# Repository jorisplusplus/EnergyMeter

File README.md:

PCB and esphome configuration for reading P1 smart meter and RS485 Modbus devices (pv systems)

## Hardware ##
Hardware production files are found in the production folder. These files can be generated with the generate.sh command (requires kikit to be installed).

## ESPHOME ##
In the esphome folder there are 2 configuration files for P1 Meter and Goodwe xs inverter. Note both configurations use the ethernet port

## Housing ##
In the Housing folder the openscad and stl files are present. The pcb should fit pressfit in the housing.

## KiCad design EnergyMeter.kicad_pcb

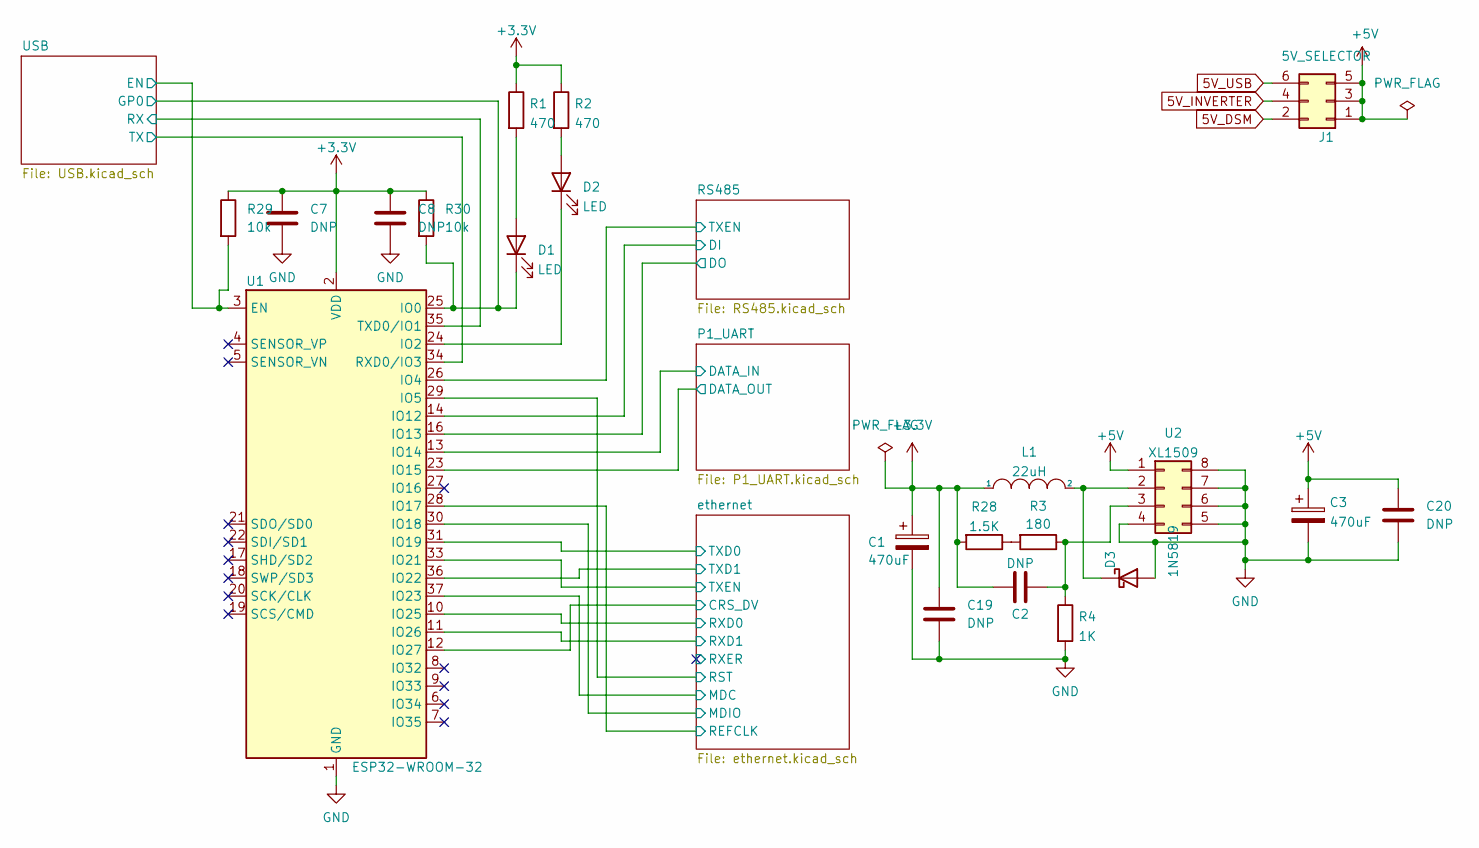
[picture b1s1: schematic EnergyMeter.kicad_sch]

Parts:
C1, C3: 470uF; CP_Radial_D8.0mm_P3.50mm; LCSC C1590895
C2, C7, C8, C19, C20: DNP; C_0603_1608Metric
D1, D2: LED; LED_0805_2012Metric; LCSC C84256
D3: 1N5819; D_SOD-323; LCSC C191023
J1: 5V_SELECTOR; PinHeader_2x03_P2.54mm_Horizontal
L1: 22uH; L_Taiyo-Yuden_NR-40xx; LCSC C83472
R1, R2: 470; R_0603_1608Metric; LCSC C23179
R3: 180; R_0603_1608Metric; LCSC C22828
R4: 1K; R_0603_1608Metric; LCSC C21190
R28: 1.5K; R_0603_1608Metric; LCSC C22843
R29, R30: 10k; R_0603_1608Metric
U1: ESP32-WROOM-32; LCSC C82899
U2: XL1509; SOP-8_3.9x4.9mm_P1.27mm; LCSC C74192

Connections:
5V_DSM: J1.2; also elsewhere on the board
5V_INVERTER: J1.4; also elsewhere on the board
5V_USB: J1.6; also elsewhere on the board
+3V3: C1.1, C2.1, C7.1, C8.1, C19.1, L1.1, R1.1, R2.1, R28.2, R29.1, R30.1, U1.2 (VDD); also elsewhere on the board
+5V: C3.1, C20.1, J1.1, J1.3, J1.5, U2.1; also elsewhere on the board
/P1_UART/DATA_IN: U1.13 (IO14); also elsewhere on the board
/P1_UART/DATA_OUT: U1.23 (IO15); also elsewhere on the board
/RS485/DI: U1.14 (IO12); also elsewhere on the board
/RS485/DO: U1.16 (IO13); also elsewhere on the board
/RS485/TXEN: U1.26 (IO4); also elsewhere on the board
/USB/EN: R29.2, U1.3 (EN); also elsewhere on the board
/USB/GP0: D1.1 (K), R30.2, U1.25 (IO0); also elsewhere on the board
/USB/RX: U1.35 (TXD0/IO1); also elsewhere on the board
/USB/TX: U1.34 (RXD0/IO3); also elsewhere on the board
/ethernet/CRS_DV: U1.12 (IO27); also elsewhere on the board
/ethernet/MDC: U1.37 (IO23); also elsewhere on the board
/ethernet/MDIO: U1.30 (IO18); also elsewhere on the board
/ethernet/REFCLK: U1.28 (IO17); also elsewhere on the board
/ethernet/RST: U1.29 (IO5); also elsewhere on the board
/ethernet/RXD0: U1.10 (IO25); also elsewhere on the board
/ethernet/RXD1: U1.11 (IO26); also elsewhere on the board
/ethernet/TXD0: U1.31 (IO19); also elsewhere on the board
/ethernet/TXD1: U1.36 (IO22); also elsewhere on the board
/ethernet/TXEN: U1.33 (IO21); also elsewhere on the board
GND: C1.2, C3.2, C7.2, C8.2, C19.2, C20.2, D3.2 (A), R4.2, U1.1 (GND), U1.15 (GND), U1.38 (GND), U1.39 (GND), U2.4, U2.5, U2.6, U2.7, U2.8; also elsewhere on the board
unnamed: C2.2, R3.1, R4.1, U2.3
unnamed: D1.2 (A), R1.2
unnamed: D2.1 (K), U1.24 (IO2)
unnamed: D2.2 (A), R2.2
unnamed: D3.1 (K), L1.2, U2.2
unnamed: R3.2, R28.1

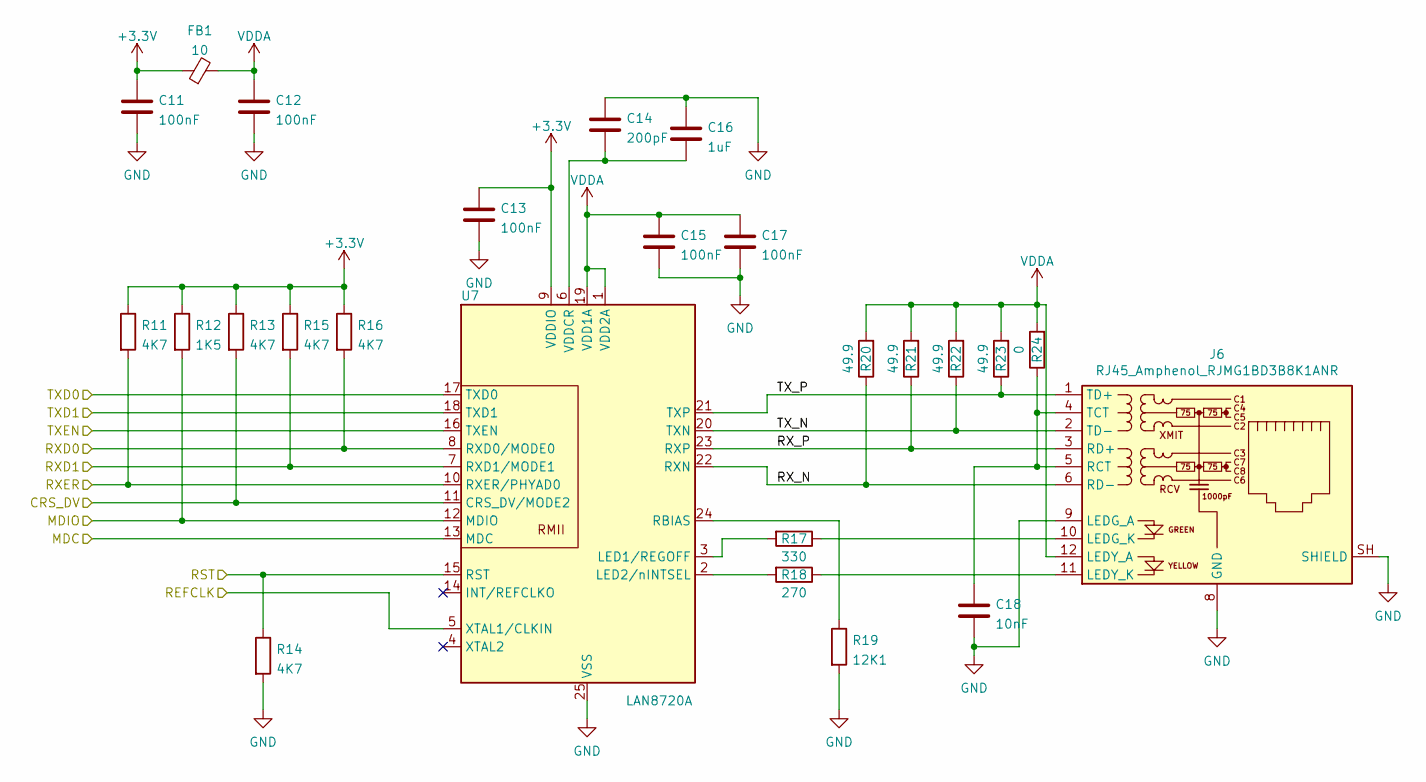
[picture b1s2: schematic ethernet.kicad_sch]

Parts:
C11, C12, C13, C15, C17: 100nF; C_0603_1608Metric; LCSC C14663
C14: 200pF; C_0603_1608Metric; LCSC C1600
C16: 1uF; C_0603_1608Metric; LCSC C15849
C18: 10nF; C_0603_1608Metric; LCSC C57112
FB1: 10; R_0805_2012Metric; LCSC C1017
J6: RJ45_Amphenol_RJMG1BD3B8K1ANR; RJ45_Hanrun_HR911105A; LCSC C12074
R11, R13, R14, R15, R16: 4K7; R_0603_1608Metric; LCSC C23162
R12: 1K5; R_0603_1608Metric; LCSC C22843
R17: 330; R_0603_1608Metric; LCSC C23138
R18: 270; R_0603_1608Metric; LCSC C22966
R19: 12K1; R_0603_1608Metric
R20, R21, R22, R23: 49.9; R_0603_1608Metric; LCSC C23185
R24: 0; R_0603_1608Metric; LCSC C21189
U7: LAN8720A; QFN-24-1EP_4x4mm_P0.5mm_EP2.6x2.6mm; LCSC C45223

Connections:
+3V3: C11.2, C13.2, FB1.1, R11.1, R12.1, R13.1, R15.1, R16.1, U7.9 (VDDIO); also elsewhere on the board
/ethernet/CRS_DV: R13.2, U7.11 (CRS_DV/MODE2); also elsewhere on the board
/ethernet/MDC: U7.13 (MDC); also elsewhere on the board
/ethernet/MDIO: R12.2, U7.12 (MDIO); also elsewhere on the board
/ethernet/REFCLK: U7.5 (XTAL1/CLKIN); also elsewhere on the board
/ethernet/RST: R14.1, U7.15 (RST); also elsewhere on the board
/ethernet/RXD0: R16.2, U7.8 (RXD0/MODE0); also elsewhere on the board
/ethernet/RXD1: R15.2, U7.7 (RXD1/MODE1); also elsewhere on the board
/ethernet/RXER: R11.2, U7.10 (RXER/PHYAD0)
/ethernet/RX_N: J6.6 (RD-), R20.1, U7.22 (RXN)
/ethernet/RX_P: J6.3 (RD+), R21.1, U7.23 (RXP)
/ethernet/TXD0: U7.17 (TXD0); also elsewhere on the board
/ethernet/TXD1: U7.18 (TXD1); also elsewhere on the board
/ethernet/TXEN: U7.16 (TXEN); also elsewhere on the board
/ethernet/TX_N: J6.2 (TD-), R22.1, U7.20 (TXN)
/ethernet/TX_P: J6.1 (TD+), R23.1, U7.21 (TXP)
GND: C11.1, C12.1, C13.1, C14.1, C15.1, C16.1, C17.1, C18.2, J6.8 (GND), J6.9 (LEDG_A), J6.SH (SHIELD), R14.2, R19.2, U7.25 (VSS); also elsewhere on the board
unnamed: C14.2, C16.2, U7.6 (VDDCR)
unnamed: C18.1, J6.4 (TCT), J6.5 (RCT), R24.1
unnamed: J6.10 (LEDG_K), R17.1
unnamed: J6.11 (LEDY_K), R18.1
unnamed: R17.2, U7.3 (LED1/REGOFF)
unnamed: R18.2, U7.2 (LED2/nINTSEL)
unnamed: R19.1, U7.24 (RBIAS)
VDDA: C12.2, C15.2, C17.2, FB1.2, J6.12 (LEDY_A), R20.2, R21.2, R22.2, R23.2, R24.2, U7.1 (VDD2A), U7.19 (VDD1A)

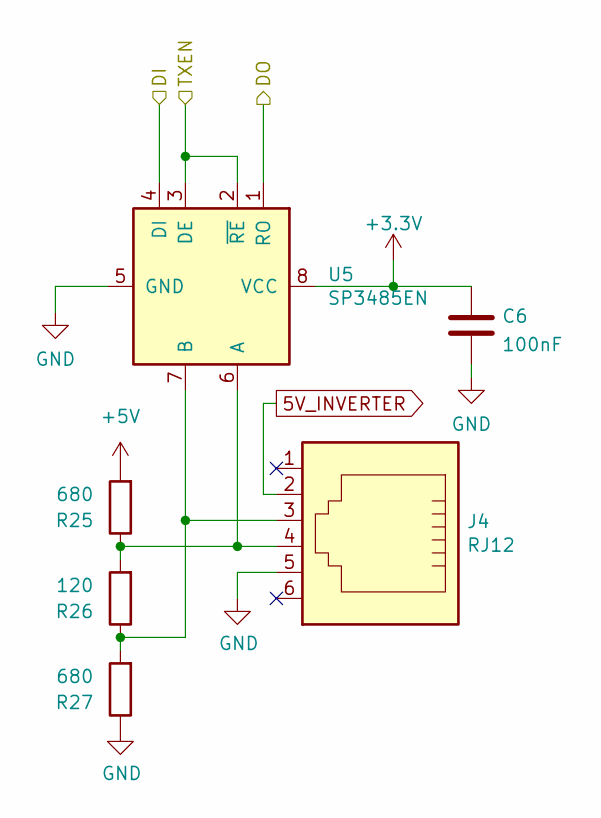
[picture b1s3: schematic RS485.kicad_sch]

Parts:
C6: 100nF; C_0603_1608Metric; LCSC C14663
J4: RJ12; RJ12_Amphenol_54601; LCSC C305981
R25, R27: 680; R_0603_1608Metric; LCSC C23228
R26: 120; R_0603_1608Metric; LCSC C22787
U5: SP3485EN; SOIC-8_3.9x4.9mm_P1.27mm; LCSC C8963

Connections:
5V_INVERTER: J4.2; also elsewhere on the board
+3V3: C6.1, U5.8 (VCC); also elsewhere on the board
+5V: R25.2; also elsewhere on the board
/RS485/DI: U5.4 (DI); also elsewhere on the board
/RS485/DO: U5.1 (RO); also elsewhere on the board
/RS485/TXEN: U5.2 (~RE), U5.3 (DE); also elsewhere on the board
GND: C6.2, J4.5, R27.1, U5.5 (GND); also elsewhere on the board
unnamed: J4.3, R26.1, R27.2, U5.7 (B)
unnamed: J4.4, R25.1, R26.2, U5.6 (A)

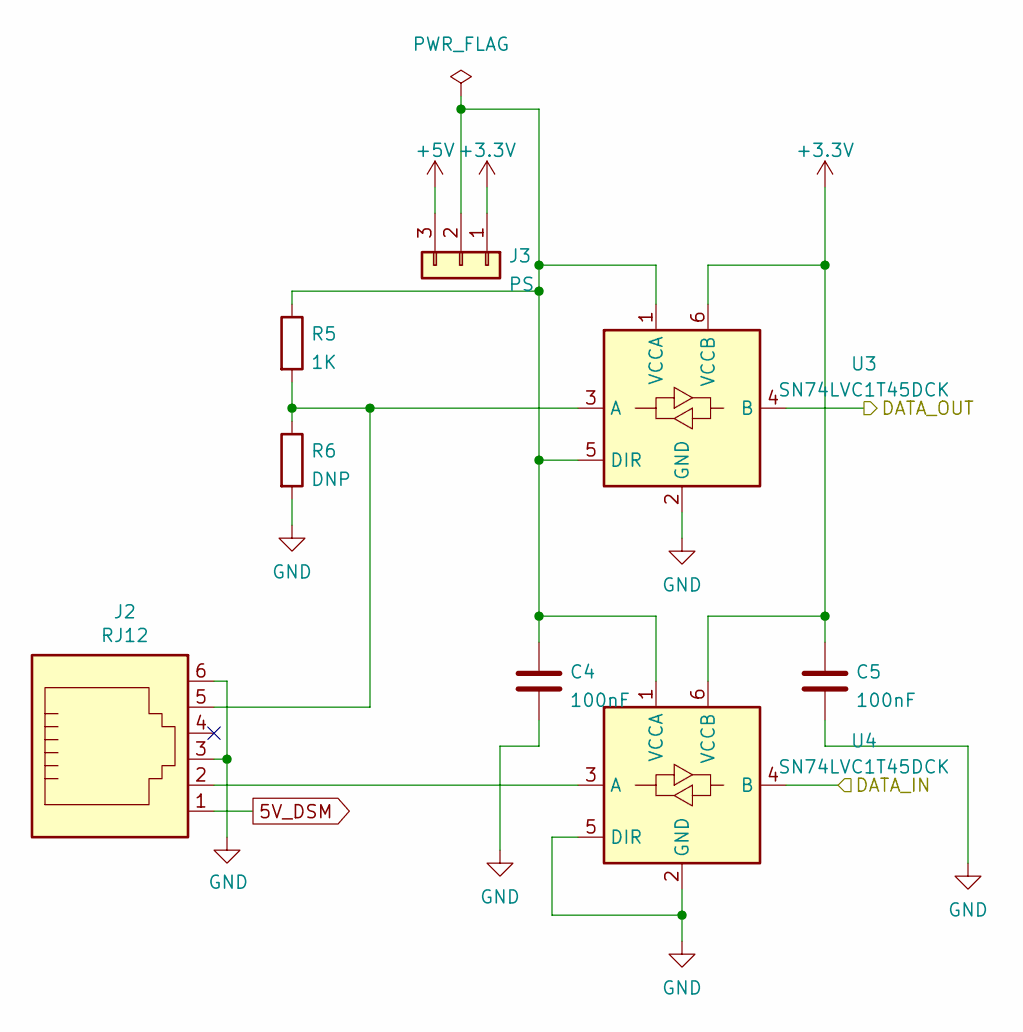
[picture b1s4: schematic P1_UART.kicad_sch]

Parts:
C4, C5: 100nF; C_0603_1608Metric; LCSC C14663
J2: RJ12; RJ12_Amphenol_54601; LCSC C305981
J3: PS; PinHeader_1x03_P2.54mm_Vertical
R5: 1K; R_0603_1608Metric; LCSC C21190
R6: DNP; R_0603_1608Metric
U3, U4: SN74LVC1T45DCK; SOT-363_SC-70-6; LCSC C133077

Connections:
5V_DSM: J2.1; also elsewhere on the board
+3V3: C5.1, J3.1, U3.6 (VCCB), U4.6 (VCCB); also elsewhere on the board
+5V: J3.3; also elsewhere on the board
/P1_UART/DATA_IN: U4.4 (B); also elsewhere on the board
/P1_UART/DATA_OUT: U3.4 (B); also elsewhere on the board
GND: C4.2, C5.2, J2.3, J2.6, R6.2, U3.2 (GND), U4.2 (GND), U4.5 (DIR); also elsewhere on the board
unnamed: C4.1, J3.2, R5.1, U3.1 (VCCA), U3.5 (DIR), U4.1 (VCCA)
unnamed: J2.2, U4.3 (A)
unnamed: J2.5, R5.2, R6.1, U3.3 (A)

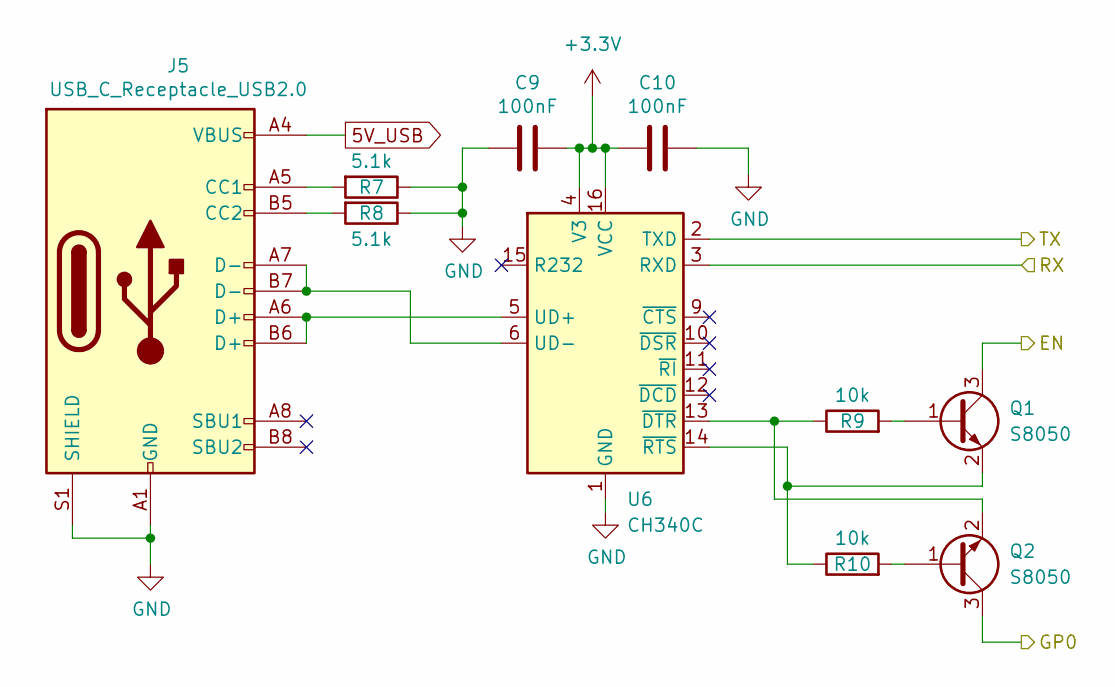
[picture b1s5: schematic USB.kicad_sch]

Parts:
C9, C10: 100nF; C_0603_1608Metric; LCSC C14663
J5: USB_C_Receptacle_USB2.0; USB_C_Receptacle_HRO_TYPE-C-31-M-12; LCSC C165948
Q1, Q2: S8050; SOT-23; LCSC C2146
R7, R8: 5.1k; R_0603_1608Metric; LCSC C23186
R9, R10: 10k; R_0603_1608Metric; LCSC C25804
U6: CH340C; SOIC-16_3.9x9.9mm_P1.27mm; LCSC C84681

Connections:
5V_USB: J5.A4 (VBUS), J5.A9 (VBUS), J5.B4 (VBUS), J5.B9 (VBUS); also elsewhere on the board
+3V3: C9.1, C10.2, U6.4 (V3), U6.16 (VCC); also elsewhere on the board
/USB/EN: Q1.3 (C); also elsewhere on the board
/USB/GP0: Q2.3 (C); also elsewhere on the board
/USB/RX: U6.3 (RXD); also elsewhere on the board
/USB/TX: U6.2 (TXD); also elsewhere on the board
GND: C9.2, C10.1, J5.A1 (GND), J5.A12 (GND), J5.B1 (GND), J5.B12 (GND), J5.S1 (SHIELD), R7.1, R8.1, U6.1 (GND); also elsewhere on the board
unnamed: J5.A5 (CC1), R7.2
unnamed: J5.A6 (D+), J5.B6 (D+), U6.5 (UD+)
unnamed: J5.A7 (D-), J5.B7 (D-), U6.6 (UD-)
unnamed: J5.B5 (CC2), R8.2
unnamed: Q1.1 (B), R9.2
unnamed: Q1.2 (E), R10.1, U6.14 (~RTS)
unnamed: Q2.1 (B), R10.2
unnamed: Q2.2 (E), R9.1, U6.13 (~DTR)

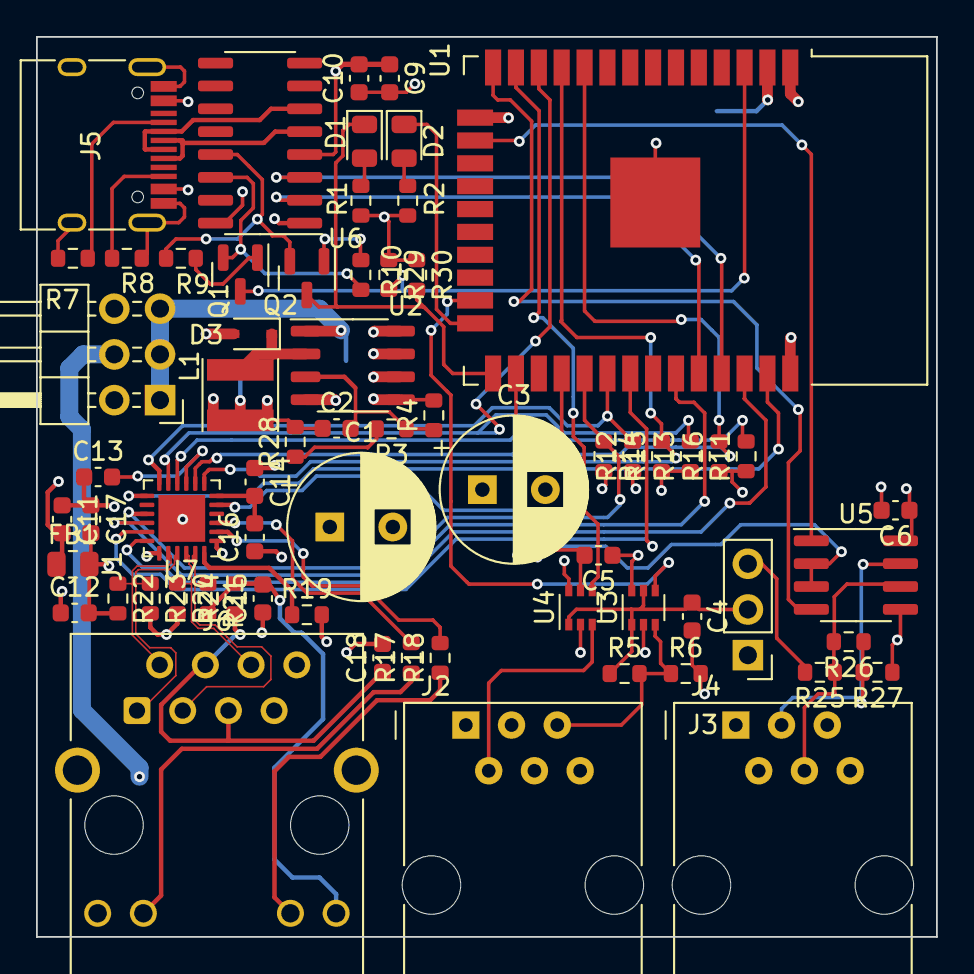
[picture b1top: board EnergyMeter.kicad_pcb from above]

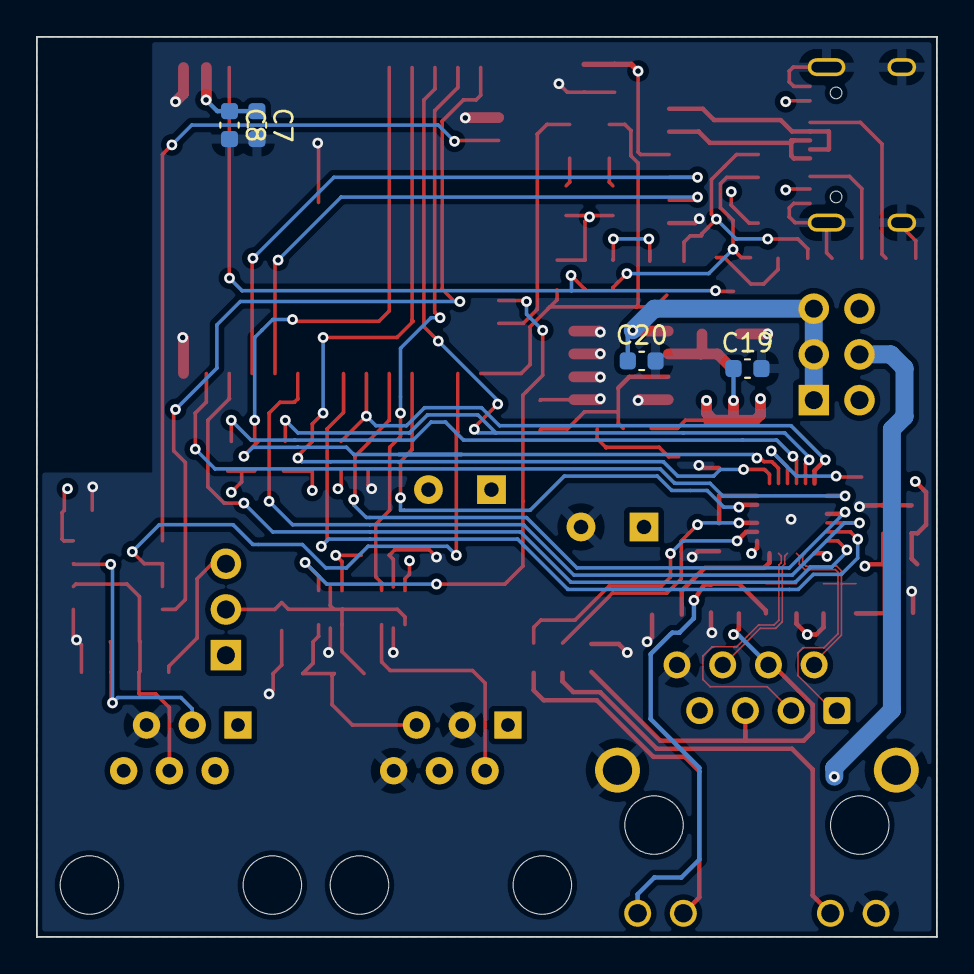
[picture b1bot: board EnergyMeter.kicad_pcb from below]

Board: 4 copper layers, 50.0 x 50.0 mm, 70 parts (4 on the bottom side), 57 nets.

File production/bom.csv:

Comment,Designator,Footprint,LCSC
470uF,"C1,C3",Capacitor_THT:CP_Radial_D8.0mm_P3.50mm,C1590895
DNP,"C2,C7,C8,C19,C20",Capacitor_SMD:C_0603_1608Metric,
100nF,"C4,C5,C6,C9,C10,C11,C12,C13,C15,C17",Capacitor_SMD:C_0603_1608Metric,C14663
200pF,C14,Capacitor_SMD:C_0603_1608Metric,C1600
1uF,C16,Capacitor_SMD:C_0603_1608Metric,C15849
10nF,C18,Capacitor_SMD:C_0603_1608Metric,C57112
LED,"D1,D2",LED_SMD:LED_0805_2012Metric,C84256
1N5819,D3,Diode_SMD:D_SOD-323,C191023
10,FB1,Resistor_SMD:R_0805_2012Metric,C1017
5V_SELECTOR,J1,Connector_PinHeader_2.54mm:PinHeader_2x03_P2.54mm_Horizontal,
RJ12,"J2,J4",Connector_RJ:RJ12_Amphenol_54601,C305981
PS,J3,Connector_PinHeader_2.54mm:PinHeader_1x03_P2.54mm_Vertical,
USB_C_Receptacle_USB2.0,J5,Connector_USB:USB_C_Receptacle_HRO_TYPE-C-31-M-12,C165948
RJ45_Amphenol_RJMG1BD3B8K1ANR,J6,Connector_RJ:RJ45_Hanrun_HR911105A,C12074
22uH,L1,Inductor_SMD:L_Taiyo-Yuden_NR-40xx,C83472
S8050,"Q1,Q2",Package_TO_SOT_SMD:SOT-23,C2146
470,"R1,R2",Resistor_SMD:R_0603_1608Metric,C23179
180,R3,Resistor_SMD:R_0603_1608Metric,C22828
1K,"R4,R5",Resistor_SMD:R_0603_1608Metric,C21190
DNP,R6,Resistor_SMD:R_0603_1608Metric,
5.1k,"R7,R8",Resistor_SMD:R_0603_1608Metric,C23186
10k,"R9,R10",Resistor_SMD:R_0603_1608Metric,C25804
4K7,"R11,R13,R14,R15,R16",Resistor_SMD:R_0603_1608Metric,C23162
1K5,R12,Resistor_SMD:R_0603_1608Metric,C22843
330,R17,Resistor_SMD:R_0603_1608Metric,C23138
270,R18,Resistor_SMD:R_0603_1608Metric,C22966
12K1,R19,Resistor_SMD:R_0603_1608Metric,
49.9,"R20,R21,R22,R23",Resistor_SMD:R_0603_1608Metric,C23185
0,R24,Resistor_SMD:R_0603_1608Metric,C21189
680,"R25,R27",Resistor_SMD:R_0603_1608Metric,C23228
120,R26,Resistor_SMD:R_0603_1608Metric,C22787
1.5K,R28,Resistor_SMD:R_0603_1608Metric,C22843
10k,"R29,R30",Resistor_SMD:R_0603_1608Metric,
ESP32-WROOM-32,U1,RF_Module:ESP32-WROOM-32,C82899
XL1509,U2,Package_SO:SOP-8_3.9x4.9mm_P1.27mm,C74192
SN74LVC1T45DCK,"U3,U4",Package_TO_SOT_SMD:SOT-363_SC-70-6,C133077
SP3485EN,U5,Package_SO:SOIC-8_3.9x4.9mm_P1.27mm,C8963
CH340C,U6,Package_SO:SOIC-16_3.9x9.9mm_P1.27mm,C84681
LAN8720A,U7,Package_DFN_QFN:QFN-24-1EP_4x4mm_P0.5mm_EP2.6x2.6mm,C45223

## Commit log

2022-07-19 Added readme
